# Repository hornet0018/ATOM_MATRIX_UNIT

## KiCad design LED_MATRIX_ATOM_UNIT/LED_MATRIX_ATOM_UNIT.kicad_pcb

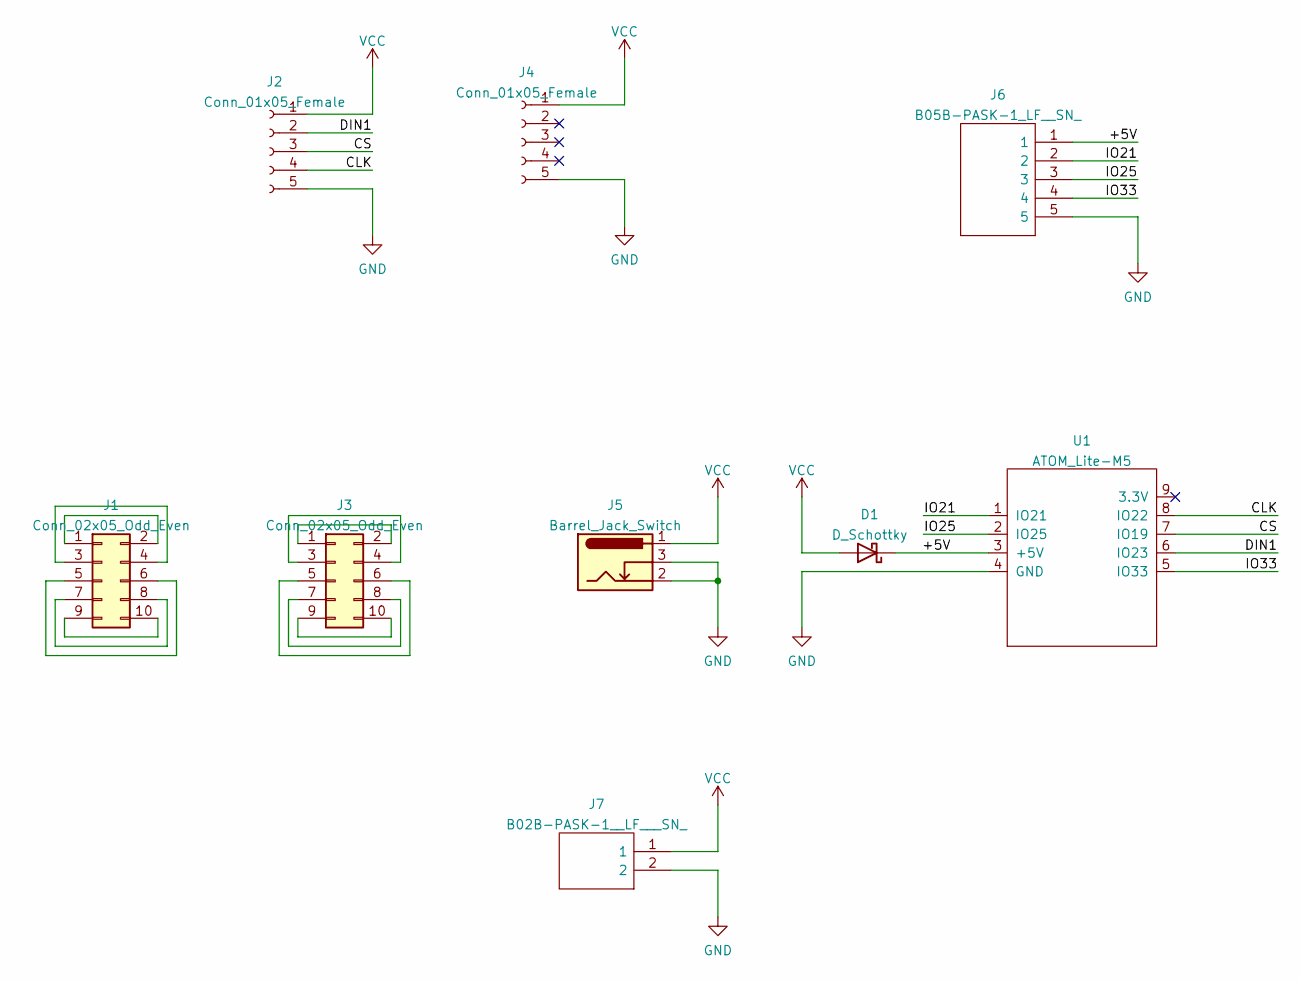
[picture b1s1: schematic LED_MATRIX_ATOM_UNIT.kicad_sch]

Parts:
D1: D_Schottky; D_SOD-123F
J1, J3: Conn_02x05_Odd_Even; PinSocket_2x05_P2.00mm_Vertical
J2, J4: Conn_01x05_Female; PinSocket_1x05_P2.00mm_Vertical
J5: Barrel_Jack_Switch; MJ179PH
J6: B05B-PASK-1_LF__SN_; B05BPASK1LFSN; Manufacturer_Part_Number B05B-PASK-1(LF)(SN)
J7: B02B-PASK-1__LF___SN_; B02BPASK1LFSN; Manufacturer_Part_Number B02B-PASK-1 (LF) (SN)
U1: ATOM_Lite-M5; M5ATOM

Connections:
/+5V: D1.1 (K), J6.1, U1.3 (+5V)
/CLK: J2.4, U1.8 (IO22)
/CS: J2.3, U1.7 (IO19)
/DIN1: J2.2, U1.6 (IO23)
/IO21: J6.2, U1.1 (IO21)
/IO25: J6.3, U1.2 (IO25)
/IO33: J6.4, U1.5 (IO33)
GND: J2.5, J4.5, J5.2, J5.3, J6.5, J7.2, U1.4 (GND)
unnamed: J1.1, J1.2
unnamed: J1.3, J1.4
unnamed: J1.5, J1.6
unnamed: J1.7, J1.8
unnamed: J1.9, J1.10
unnamed: J3.1, J3.2
unnamed: J3.3, J3.4
unnamed: J3.5, J3.6
unnamed: J3.7, J3.8
unnamed: J3.9, J3.10
VCC: D1.2 (A), J2.1, J4.1, J5.1, J7.1

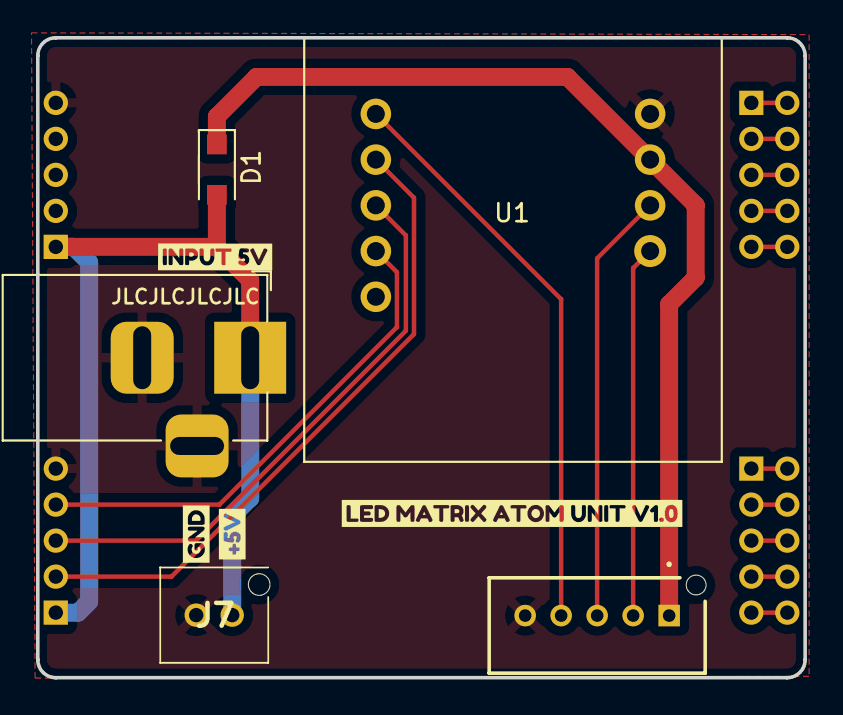
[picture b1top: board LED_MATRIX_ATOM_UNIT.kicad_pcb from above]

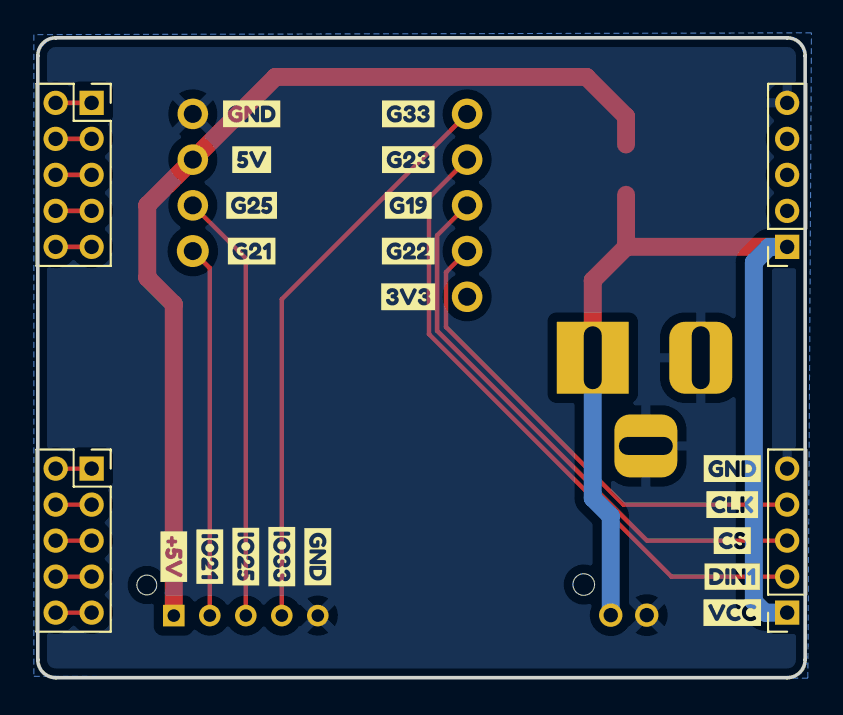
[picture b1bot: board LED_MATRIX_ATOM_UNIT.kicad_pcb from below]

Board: 2 copper layers, 42.6 x 35.5 mm, 32 parts (23 on the bottom side), 19 nets.

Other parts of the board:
kibuzzard-636A4C3A: G***; kibuzzard-636A4C3A
kibuzzard-636A4C4F: G***; kibuzzard-636A4C4F
kibuzzard-636A4C5F: G***; kibuzzard-636A4C5F
kibuzzard-636A4C45: G***; kibuzzard-636A4C45
kibuzzard-636A4C56: G***; kibuzzard-636A4C56
kibuzzard-636A31DF: G***; kibuzzard-636A31DF
kibuzzard-636A31F2: G***; kibuzzard-636A31F2
kibuzzard-636A34D8: G***; kibuzzard-636A34D8
kibuzzard-636A46AD: G***; kibuzzard-636A46AD
kibuzzard-636A46C3: G***; kibuzzard-636A46C3
kibuzzard-636A321D: G***; kibuzzard-636A321D
kibuzzard-636A3201: G***; kibuzzard-636A3201
kibuzzard-636A3210: G***; kibuzzard-636A3210
kibuzzard-636A3261: G***; kibuzzard-636A3261
kibuzzard-636A3268: G***; kibuzzard-636A3268
kibuzzard-6369B8DB: G***; kibuzzard-6369B8DB
kibuzzard-6369B91F: G***; kibuzzard-6369B91F
kibuzzard-6369B92E: G***; kibuzzard-6369B92E
kibuzzard-6369B912: G***; kibuzzard-6369B912
kibuzzard-6369B927: G***; kibuzzard-6369B927
kibuzzard-6369B937: G***; kibuzzard-6369B937
kibuzzard-6369BB57: G***; kibuzzard-6369BB57
kibuzzard-6369BB69: G***; kibuzzard-6369BB69

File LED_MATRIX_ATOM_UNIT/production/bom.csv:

Designator,Footprint,Quantity,Value,LCSC Part #
D1,D_SOD-123F,1,D_Schottky,
"J1, J3",PinSocket_2x05_P2.00mm_Vertical,2,Conn_02x05_Odd_Even,
"J2, J4",PinSocket_1x05_P2.00mm_Vertical,2,Conn_01x05_Female,
J5,MJ179PH,1,Barrel_Jack_Switch,
U1,M5ATOM,1,ATOM_Lite-M5,

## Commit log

2022-11-08 create production data
